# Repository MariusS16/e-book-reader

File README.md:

# README - OpenBook E-Reader

**Autor: Slincu Marius**

## Prezentare Generală

OpenBook este un e-reader open-source bazat pe microcontrollerul ESP32-C6. Dispozitivul integrează un ecran e-paper de 7.5 inch, un senzor de mediu (BME680), un sistem de monitorizare a bateriei, precum și conectivitate Wi-Fi și USB-C. Acest fisier descrie arhitectura hardware a proiectului, componentele principale și modul în care acestea sunt interconectate.

---

## Diagramă de Bloc

```

                +---------------------------+
                |     USB-C Connector       |
                | (USB Data ↔ ESP32 USB)    |
                | (ESD & Termination Prot.) |
                +-------------+-------------+
                              |
                              v
                +--------------------------+
                |       Charging IC        |<-- USB-C Power
                +-------------+------------+
                              |
                              v
                +--------------------------+
                |         Battery          |
                +-------------+------------+
                              |
                              v
                +--------------------------+
                |           LDO            |
                |       (3.3V Reg)         |
                +-------------+------------+
                              |
                              v
                      +--------------+
                      |    ESP32-C6   |
                      +------+--------+
                             |
      +----------------------+-------------------------+
      |                      |                         |
      v                      v                         v
+-----------+       +----------------+         +-----------------+
|  Display  |<----->|     BME688     |<------->| Tactile Buttons |
| (SPI 4W)  |       |   (I2C + PU)   |         |  (GPIO + RC)     |
+-----------+       +----------------+         +-----------------+
```

---
## Detalii Hardware

### ESP32-C6-WROOM-1-N8

- **Rol**: Componenta centrală de control, responsabilă pentru conectivitatea wireless și interacțiunea cu perifericele.
- **Interfețe disponibile**:
  - SPI: Utilizată pentru comunicarea cu ecranul e-paper, memoria Flash și cardul Micro SD.
  - I2C: Pentru conectarea senzorului BME680, monitorului de baterie (MAX17048) și ceasului RTC (DS3231).
  - GPIO: Utilizați pentru butoane de control și semnalizare prin LED-uri.
  - UART: Dedicat depanării și comunicației seriale.
- **Specificații tehnice**: Tactat la 160MHz, 512KB SRAM, 8MB memorie Flash integrată.

### Senzor BME680

- **Rol**: Oferă măsurători precise pentru temperatură, umiditate, presiune atmosferică și calitatea aerului.
- **Interfață**: Comunicare prin magistrala I2C cu viteză de 400kHz.
- **Eficiență energetică**: Consumă sub 1mA în funcționare și sub 1µA în repaus.

### Sistem de Alimentare

- **Baterie**: Acumulator Li-Po de 2500mAh, 3.7V.
- **Încărcare**: Controlată de MCP73831 prin portul USB-C, cu un curent maxim de 1A.
- **Monitorizare**: Realizată cu ajutorul cipului MAX17048, prin I2C.
- **Profil de consum**:
  - În activitate (Wi-Fi activ și ecran actualizat): ~150mA.
  - În standby (ecran static, fără activitate radio): ~10mA.
  - În modul deep sleep: >50µA.
  - **Autonomie estimată**: ~250 de ore la un consum mediu de 10mA.

### Butoane de Navigare

- Folosește butoane tactile Panasonic EVQPUJ02K, fiecare cu rezistență pull-up de 10KΩ.

### USB-C

- **Funcții**: Utilizat pentru încărcare (5V/1A) și transfer de date (USB 2.0).
- **Protecție**: Diode ESD (USBLC6-2SC6Y) pentru protejarea la supratensiuni.

---
# Lista de Componente (BOM)

Tabelul de mai jos prezintă componentele folosite în proiect:
| Component | Buy | Datasheet |
| ---------- | --------- | --------- |
| PFMF.050.1 | [Retailer](https://ro.mouser.com/ProductDetail/Schurter/PFMF.050.2?qs=1auRipcfynCums5v1iucSA%3D%3D) |  [Datasheet](https://ro.mouser.com/datasheet/2/358/typ_PFMF-1275918.pdf) |
| USB4110-GF-A | [Retailer](https://ro.mouser.com/ProductDetail/GCT/USB4110-GF-A?qs=KUoIvG%2F9IlYiZvIXQjyJeA%3D%3D) | [Datasheet](https://ro.mouser.com/datasheet/2/837/GCT_USB4110_Product_Drawing___20k_cycles-3455479.pdf) |
| USBLC6-2SC6Y | [Retailer](https://ro.mouser.com/ProductDetail/STMicroelectronics/USBLC6-2SC6Y?qs=gNDSiZmRJS%2FOgDexvXkdow%3D%3D) | [Datasheet](https://ro.mouser.com/datasheet/2/389/usblc6_2sc6y-1852505.pdf) |
| SD0805S020S1R0 | [Retailer](https://ro.mouser.com/ProductDetail/KYOCERA-AVX/SD0805S020S1R0?qs=jCA%252BPfw4LHbpkAoSnwrdjw%3D%3D) | [Datasheet](https://ro.mouser.com/datasheet/2/40/schottky-3165252.pdf) |
| DMG2305UX-7 | [Retailer](https://ro.mouser.com/ProductDetail/Diodes-Incorporated/DMG2305UX-7?qs=L1DZKBg7t5F%2FNBHrjfxC%252Bg%3D%3D) | [Datasheet](https://www.diodes.com/assets/Datasheets/DMG2305UX.pdf) |
| XC6220A331MR-G | [Retailer](https://ro.mouser.com/ProductDetail/Torex-Semiconductor/XC6220A331MR-G?qs=AsjdqWjXhJ8ZSWznL1J0gg%3D%3D) | [Datasheet](https://ro.mouser.com/datasheet/2/760/xc6220-3371556.pdf) |
| Condensator 100 uF TANT | [Retailer](https://ro.mouser.com/ProductDetail/KYOCERA-AVX/TAJW107M010RNJ?qs=Wtp%252Bf%2FAeVqIH8v1VxV%252B1Rg%3D%3D) | [Datasheet](https://ro.mouser.com/datasheet/2/40/TAJ-3165264.pdf) |
| 112A-TAAR-R03_ATTEND | [Retailer](https://www.digikey.ro/en/products/detail/attend-technology/112A-TAAR-R03/17633923) | [Datasheet](https://www.attend.com.tw/data/download/file/112A-TAAR-R03_Spec.pdf)
| ESP32-C6-WROOM-1-N8 | [Retailer](https://ro.mouser.com/ProductDetail/Espressif-Systems/ESP32-C6-WROOM-1-N8?qs=8Wlm6%252BaMh8ST02Gmwp74cw%3D%3D) | [Datasheet](https://ro.mouser.com/datasheet/2/891/Espressif_ESP32_C6_WROOM_1__Datasheet_V0_1_PRELIMI-3239987.pdf) |
| MCP73831 | [Retailer](https://ro.mouser.com/ProductDetail/Microchip-Technology/MCP73831T-2ACI-OT?qs=yUQqVecv4qvbBQBGbHx0Mw%3D%3D) | [Datasheet](https://ro.mouser.com/datasheet/2/268/MCP73831_Family_Data_Sheet_DS20001984H-3441711.pdf) |
| CHG_LED | [Retailer](https://store.comet.srl.ro/Catalogue/Product/40478/) | [Datasheet](https://www.snapeda.com/parts/KP-1608SURCK/Kingbright/datasheet/) |
| SI1308EDL-T1-GE3 | [Retailer](https://ro.mouser.com/ProductDetail/Vishay-Semiconductors/SI1308EDL-T1-GE3?qs=bX1%252BNvsK%2FBramh9tgpOaEw%3D%3D) | [Datasheet](https://www.vishay.com/doc?63399) |
| MBR0530 | [Retailer](https://ro.mouser.com/ProductDetail/Micro-Commercial-Components-MCC/MBR0530-T?qs=9VyI4qLX4NTSXkb9ynzJnA%3D%3D) | [Datasheet](https://ro.mouser.com/datasheet/2/258/mcc_mbr0520~mbr0560sod123-1179695.pdf) |
| L1 | [Retailer](https://ro.mouser.com/ProductDetail/Wurth-Elektronik/744043680?qs=PGXP4M47uW6VkZq%252BkzjrHA%3D%3D) | [Datasheet](https://www.we-online.com/components/products/datasheet/744043680.pdf) |
| FH34SRJ-24S-0.5SH_99_ | [Retailer](https://ro.mouser.com/ProductDetail/Hirose-Connector/FH34SRJ-24S-0.5SH99?qs=vcbW%252B4%252BSTIpKBl5ap9J8Fw%3D%3D) | [Datasheet](https://ro.mouser.com/datasheet/2/185/FH34SRJ_24S_0_5SH_99__CL0580_1255_6_99_2DDrawing_0-1615044.pdf) |
| BME688 | [Retailer](https://ro.mouser.com/ProductDetail/Bosch-Sensortec/BME688?qs=IS%252B4QmGtzzqQoVDscqwx3A%3D%3D) | [Datasheet](https://ro.mouser.com/datasheet/2/783/bst_bme688_fl000-2307034.pdf) |
| BD5229G-TR | [Retailer](https://ro.mouser.com/ProductDetail/ROHM-Semiconductor/BD5229G-TR?qs=4kLU8WoGk0vvnhrrYwdszw%3D%3D) | [Datasheet](https://fscdn.rohm.com/en/products/databook/datasheet/ic/power/voltage_detector/bd52xxg-e.pdf) |
| Button | [Retailer](https://ro.mouser.com/ProductDetail/CK/KMR221GULCLFS?qs=u2NJ%252B70r0goBXaNk7IrU0Q%3D%3D) | [Datasheet](https://www.ckswitches.com/media/1479/kmr2.pdf) |
| MAX17048G+T10 | [Retailer](https://ro.mouser.com/ProductDetail/Analog-Devices-Maxim-Integrated/MAX17048G%2bT10?qs=D7PJwyCwLAoGnnn8jEPRBQ%3D%3D) | [Datasheet](https://ro.mouser.com/datasheet/2/609/MAX17048_MAX17049-3469099.pdf) |
| W25Q512JVEIQ | [Retailer](https://ro.mouser.com/ProductDetail/Winbond/W25Q512JVEIQ?qs=l7cgNqFNU1jw6svr3at6tA%3D%3D) | [Datasheet](https://ro.mouser.com/datasheet/2/949/Winbond_W25Q512JV_Datasheet-3240039.pdf) |
| PGB1010603MR | [Retailer](https://ro.mouser.com/ProductDetail/Littelfuse/PGB1010603MRHF?qs=KvZd0dN2Zg%2FuIq6icj%252BGKA%3D%3D) | [Datasheet](https://www.littelfuse.com/media?resourcetype=datasheets&itemid=8a337998-d54d-466b-be4e-dc5bcd1f9321&filename=littelfuse_pulseguard_pgb1_datasheet.pdf) |
| QWIIC_RIGHT_ANGLE | [Retailer](https://ro.mouser.com/ProductDetail/GCT/USB4110-GF-A?qs=KUoIvG%2F9IlYiZvIXQjyJeA%3D%3D) | [Datasheet](https://ro.mouser.com/datasheet/2/837/GCT_USB4110_Product_Drawing___20k_cycles-3455479.pdf) |
| DS3231SN# | [Retailer](https://ro.mouser.com/ProductDetail/Analog-Devices-Maxim-Integrated/DS3231SN?qs=ffX8NcjNb2RmKAb9wAk9Ug%3D%3D) | [Datasheet](https://ro.mouser.com/datasheet/2/609/DS3231-3421123.pdf) |
| CPH3225A C10_SUPERCAP | [Retailer](https://ro.mouser.com/ProductDetail/Seiko-Semiconductors/CPH3225A?qs=3etwrb1wR%252BhUOph6lAO7eg%3D%3D) | [Datasheet](https://ro.mouser.com/datasheet/2/360/Seiko_Instruments_MicroBattery_E_20230330_2024Jan_-3561061.pdf) |
| Condensator 100nF | [Retailer](https://ro.mouser.com/ProductDetail/KYOCERA-AVX/06033G104ZAT2A?qs=NXubJDmysXJMPmHfVo6Z%252BA%3D%3D) | [Datasheet](https://ro.mouser.com/datasheet/2/40/KGM_Y5V-3223189.pdf) |
| Condensator 4.7uF | [Retailer](https://ro.mouser.com/ProductDetail/KYOCERA-AVX/0402ZD475MAT2A?qs=NBFAU1oqP4W4U2PCPHI0sg%3D%3D) | [Datasheet](https://ro.mouser.com/datasheet/2/40/cx5r_KGM-3223198.pdf) |
| Condensator 10uF | [Retailer](https://ro.mouser.com/ProductDetail/Samsung-Electro-Mechanics/CL10A106KQ8NNNL?qs=xZ%2FP%252Ba9zWqaes9JKSsob2Q%3D%3D) | [Datasheet](https://ro.mouser.com/datasheet/2/585/MLCC-1837944.pdf) |

## Configurare Pini ESP32-C6

| **Pin ESP32-C6** | **Funcție**         | **Componentă**         | **Rol**                                    |
|------------------|--------------------|------------------------|--------------------------------------------|
| GPIO0           | BOOT_BUTTON        | Buton                  | Activează modul de boot la inițializare    |
| GPIO1           | RESET_BUTTON       | Buton                  | Resetare manuală                           |
| GPIO2           | CHANGE_BUTTON      | Buton                  | Comutare între meniuri                     |
| GPIO3           | EPD_CS             | Display E-Paper        | Chip Select pentru SPI                     |
| GPIO4           | EPD_DC             | Display E-Paper        | Linie de control Date/Comenzi              |
| GPIO5           | EPD_RST            | Display E-Paper        | Reset hardware pentru ecran                |
| GPIO6           | EPD_BUSY           | Display E-Paper        | Semnal de stare pentru actualizare ecran   |
| GPIO7           | SPI_MOSI           | Display, Flash, SD     | Linie de date pentru SPI                   |
| GPIO8           | SPI_MISO           | Display, Flash, SD     | Linie de date SPI (citire)                 |
| GPIO9           | SPI_SCK            | Display, Flash, SD     | Semnal de ceas SPI                         |
| GPIO10          | FLASH_CS           | Memorie Flash          | Chip Select pentru memorie                 |
| GPIO11          | SD_CS              | Card Micro SD          | Chip Select pentru card SD                 |
| GPIO12          | I2C_SDA            | BME680, MAX17048, DS3231 | Linie de date I2C                         |
| GPIO13          | I2C_SCL            | BME680, MAX17048, DS3231 | Linie de ceas I2C                         |
| GPIO14          | CHG_LED            | LED                    | Indicator al procesului de încărcare       |
| GPIO15          | UART_TX            | Debugging              | Transmitere date prin UART                 |
| GPIO16          | UART_RX            | Debugging              | Recepție date prin UART                    |
| GPIO17          | USB_D+             | USB-C                  | Linie de date USB pozitivă                 |
| GPIO18          | USB_D-             | USB-C                  | Linie de date USB negativă                 |

**Notă**: Pinii sunt alocați conform specificațiilor ESP32-C6 și necesităților proiectului OpenBook. Mulți dintre ei pot îndeplini funcții multiple și pot fi configurați flexibil în funcție de aplicație.

**Notă**: Am avut o problema cu Fusion si mi-a dat crash aplicatia si am capatat o eroare de care nu am stiut sa scap si nu am mai putu contiuna modelul 3D, insa am facut partial din ea.

---

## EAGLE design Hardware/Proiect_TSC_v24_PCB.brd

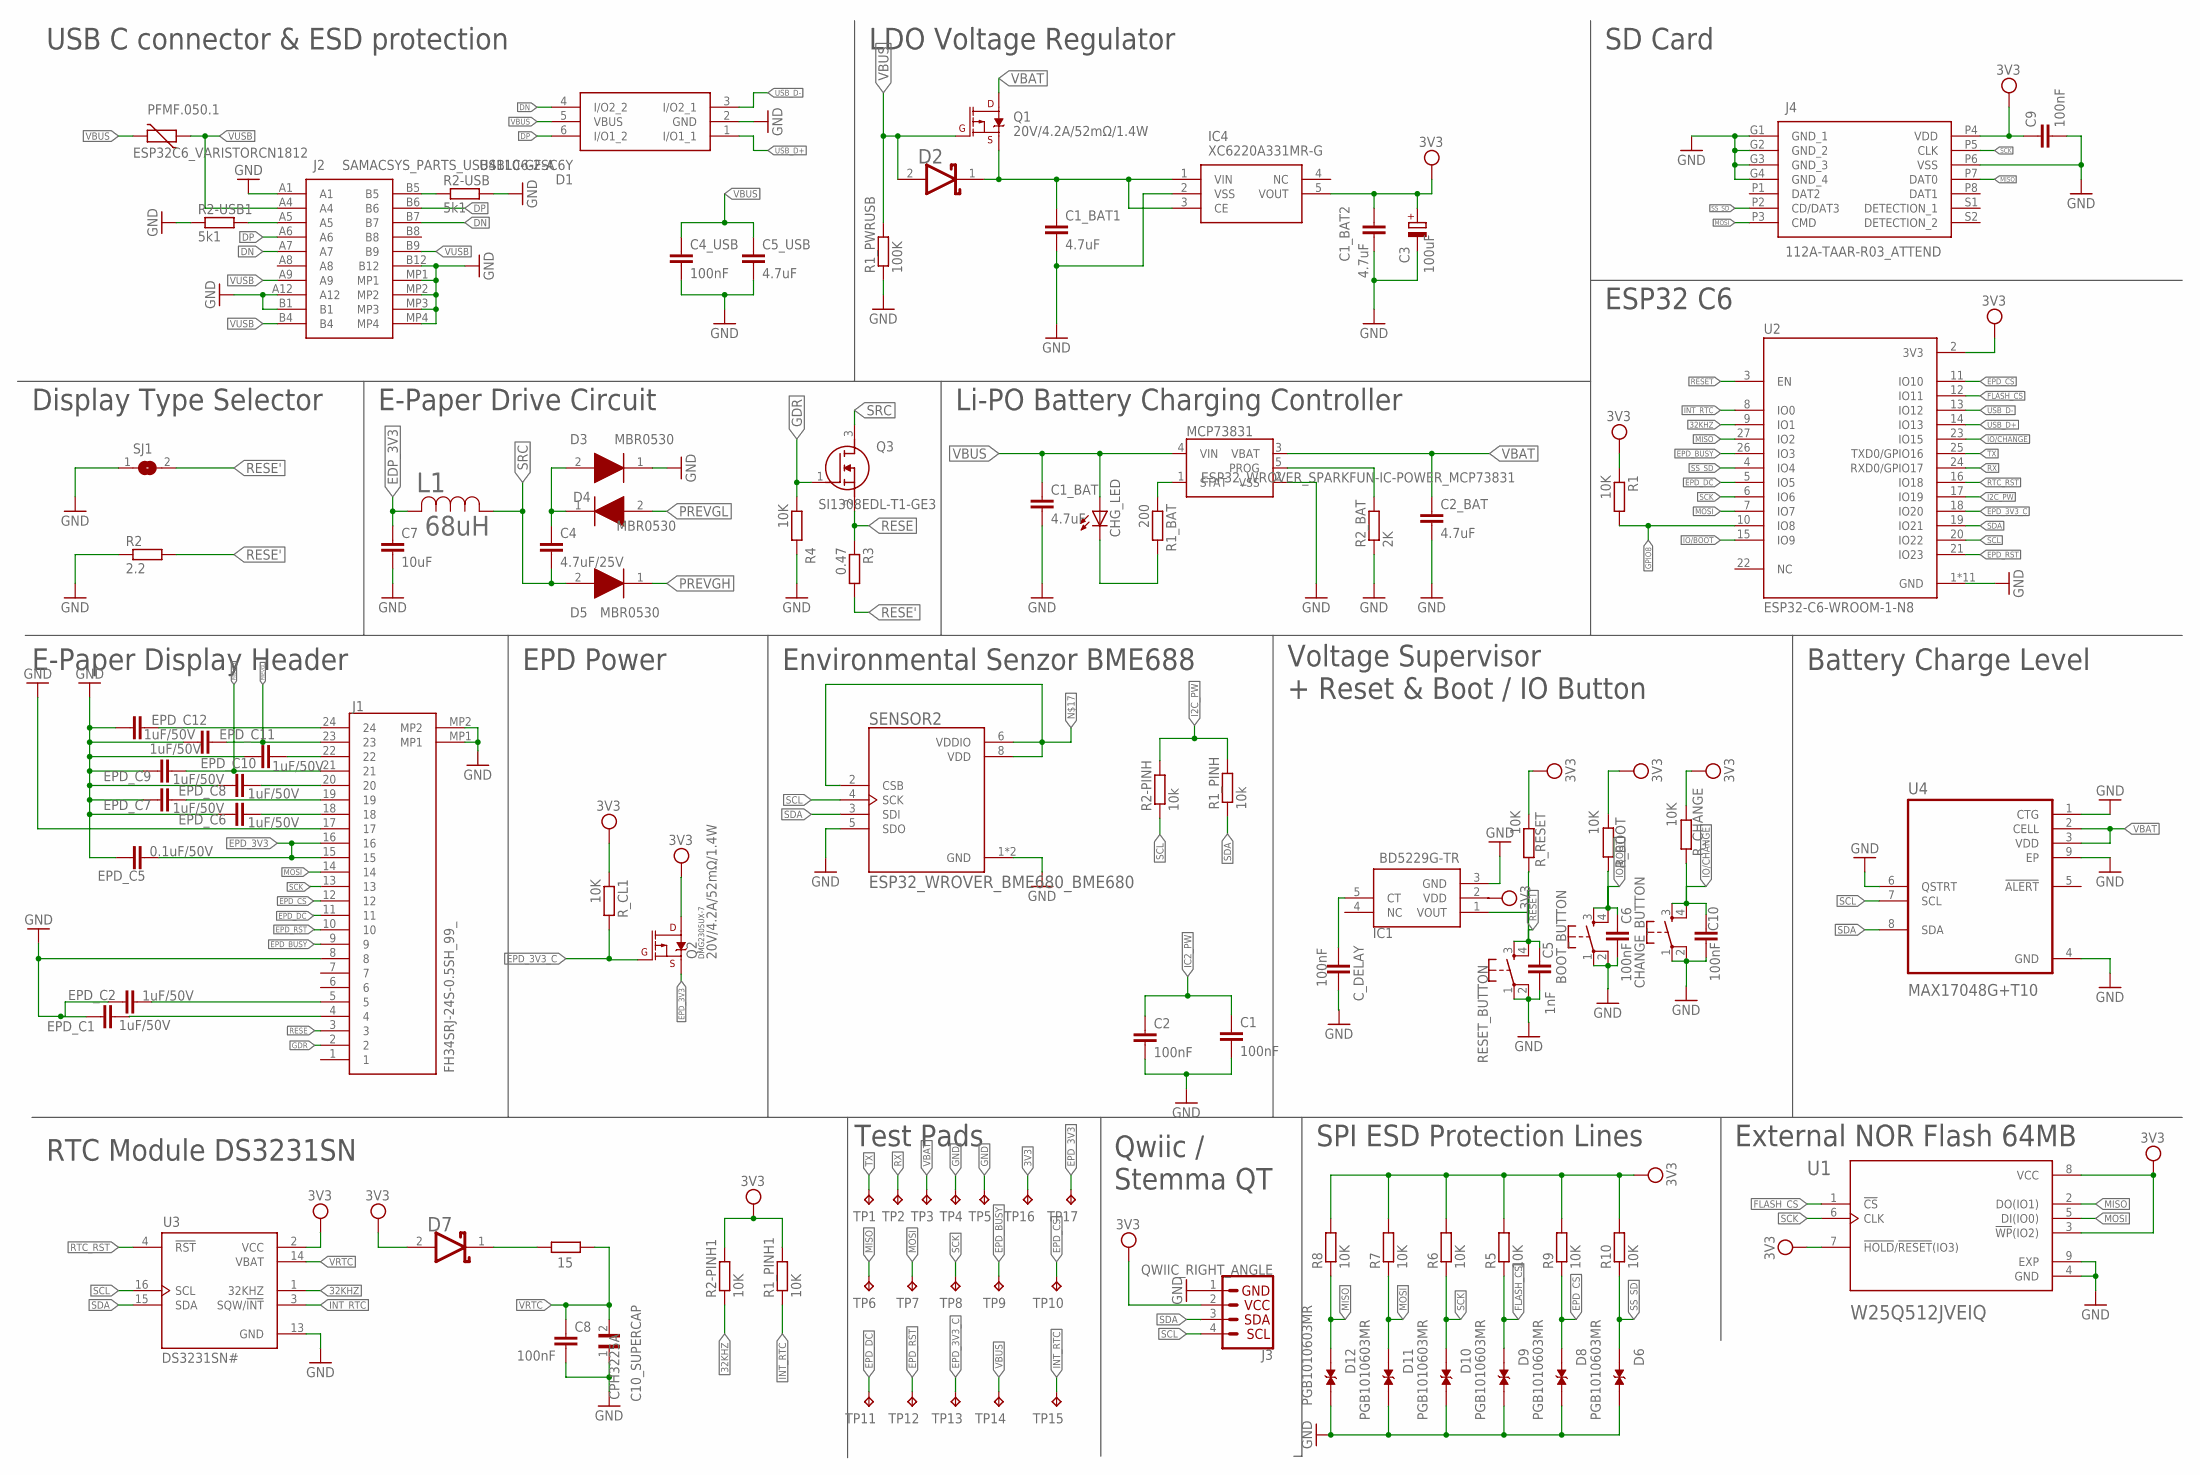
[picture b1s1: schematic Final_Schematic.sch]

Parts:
BOOT_BUTTON: BUTTON_CUSYOMV1; MYBUTTON
C1, C2, C4_USB, C8, C9: 100nF; ESP32_WROVER_EAGLE-LTSPICE_C0402
C1_BAT, C1_BAT1, C1_BAT2, C2_BAT, C5_USB: 4.7uF; ESP32_WROVER_EAGLE-LTSPICE_C0402
C3: 100uF; RCL_CT3528
C4: 4.7uF/25V; ESP32_WROVER_EAGLE-LTSPICE_C0402
C5: 1nF; EAGLE-LTSPICE_C0402
C6, C10: 100nF; EAGLE-LTSPICE_C0402
C7: 10uF; ESP32_WROVER_EAGLE-LTSPICE_C0402
C10_SUPERCAP: CPH3225A; CAPCP3225X100N
CHANGE_BUTTON: BUTTON_CUSYOMV1; MYBUTTON
CHG_LED: ADAFRUIT_LEDCHIP-LED0603; ADAFRUIT_CHIP-LED0603
C_DELAY: 100nF; ESP32_WROVER_EAGLE-LTSPICE_C0402
D1: USBLC6-2SC6Y; SOT95P280X145-6N
D2, D7: ESP32_WROVER_AVX---SD0805S020S1R0_AVX_SD0805S020S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; ESP32_WROVER_AVX---SD0805S020S1R0_AVX_SD0805S020S1R0_0
D3, D4, D5: MBR0530; SOD3716X135N
D6, D8, D9, D10, D11, D12: PGB1010603MR; DIOC1608X36N
EPD_C1, EPD_C2, EPD_C6, EPD_C7, EPD_C8, EPD_C9, EPD_C10, EPD_C11, EPD_C12: 1uF/50V; EAGLE-LTSPICE_C0402
EPD_C5: 0.1uF/50V; EAGLE-LTSPICE_C0402
IC1: BD5229G-TR; SOT95P280X125-5N
IC4: XC6220A331MR-G; SOT95P280X120-5N
J1: FH34SRJ-24S-0.5SH_99_; FH34SRJ24S05SH99
J2: SAMACSYS_PARTS_USB4110-GF-A; SAMACSYS_PARTS_USB4110GFA
J3: QWIIC_RIGHT_ANGLE; JST04_1MM_RA
J4: 112A-TAAR-R03_ATTEND; 112ATAARR03ATTEND
L1: 68uH; IND_4828-WE-TPC_WRE
MCP73831: ESP32_WROVER_SPARKFUN-IC-POWER_MCP73831; ESP32_WROVER_SPARKFUN-IC-POWER_SOT23-5
PFMF.050.1: ESP32C6_VARISTORCN1812; ESP32C6_VARISTOR_CT/CN1812
Q1, Q2: 20V/4.2A/52mΩ/1.4W; ESP32_WROVER_SPARKFUN-DISCRETESEMI_SOT23-3
Q3: SI1308EDL-T1-GE3; SOT65P210X110-3N
R1, R1_PINH1, R2-PINH1, R4, R5, R6, R7, R8, R9, R10: 10K; ESP32_WROVER_EAGLE-LTSPICE_R0402
R1_BAT: 200; ESP32_WROVER_EAGLE-LTSPICE_R0402
R1_PINH, R2-PINH: 10k; ESP32_WROVER_EAGLE-LTSPICE_R0402
R1_PWRUSB: 100K; ESP32_WROVER_EAGLE-LTSPICE_R0402
R2: 2.2; ESP32_WROVER_EAGLE-LTSPICE_R0402
R2-USB, R2-USB1: 5k1; ESP32_WROVER_EAGLE-LTSPICE_R0402
R2_BAT: 2K; ESP32_WROVER_EAGLE-LTSPICE_R0402
R3: 0.47; ESP32_WROVER_EAGLE-LTSPICE_R0402
RESET_BUTTON: BUTTON_CUSYOMV1; MYBUTTON
R_BOOT: 10K; ESP32_WROVER_EAGLE-LTSPICE_R0402
R_CAPACITOR: 15; ESP32_WROVER_EAGLE-LTSPICE_R0402
R_CHANGE: 10K; ESP32_WROVER_EAGLE-LTSPICE_R0402
R_CL1: 10K; ESP32_WROVER_EAGLE-LTSPICE_R0402
R_RESET: 10K; ESP32_WROVER_EAGLE-LTSPICE_R0402
SENSOR2: ESP32_WROVER_BME680_BME680; ESP32_WROVER_BME680_PSON80P300X300X100-8N
SJ1: SJ
TP1, TP2, TP3, TP4, TP5, TP6, TP7, TP8, TP9, TP10, TP11, TP12, TP13, TP14, TP15, TP16, TP17: TPTP20R; TP20R
U1: W25Q512JVEIQ; SON127P600X800X80-9N
U2: ESP32-C6-WROOM-1-N8; XCVR_ESP32-C6-WROOM-1-N8
U3: DS3231SN#; SOIC127P1032X265-16N
U4: MAX17048G+T10; SON50P200X200X80-9N

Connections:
3V3: C1_BAT2.1, C3.+, C9.1, D7.2 (ANODE), IC4.5 (VOUT), J3.2, J4.P4 (VDD), Q2.3 (D), R1.1, R1_PINH1.2, R2-PINH1.2, R5.2, R6.2, R7.2, R8.2, R9.2, R10.2, R_BOOT.2, R_CHANGE.2, R_CL1.1, R_RESET.2, TP16.TP, U1.3 (!WP!(IO2)), U1.7 (!HOLD!/!RESET!(IO3)), U1.8 (VCC), U2.2 (3V3), U3.2 (VCC)
32KHZ: R2-PINH1.1, U2.9 (IO1), U3.1 (32KHZ)
DN: D1.4 (I/O2_2), J2.A7, J2.B7
DP: D1.6 (I/O1_2), J2.A6, J2.B6
EDP_3V3: C7.1, L1.2
EPD_3V3: EPD_C5.2, J1.15, J1.16, Q2.2 (S), TP17.TP
EPD_3V3_C: Q2.1 (G), R_CL1.2, TP13.TP, U2.18 (IO20)
EPD_BUSY: J1.9, TP9.TP, U2.26 (IO3)
EPD_CS: D8.1, J1.12, R9.1, TP10.TP, U2.11 (IO10)
EPD_DC: J1.11, TP11.TP, U2.5 (IO5)
EPD_RST: J1.10, TP12.TP, U2.21 (IO23)
FLASH_CS: D9.1, R5.1, U1.1 (!CS), U2.12 (IO11)
GDR: J1.2, Q3.1 (G), R4.1
GND: BOOT_BUTTON.1, BOOT_BUTTON.2, C1.2, C1_BAT.2, C1_BAT1.2, C1_BAT2.2, C2.2, C2_BAT.2, C3.-, C4_USB.2, C5.2, C5_USB.2, C6.2, C7.2, C8.2, C9.2, C10.2, C10_SUPERCAP.1, CHANGE_BUTTON.1, CHANGE_BUTTON.2, C_DELAY.2, D1.2 (GND), D3.1 (K), D6.2, D8.2, D9.2, D10.2, D11.2, D12.2, EPD_C1.1, EPD_C2.1, EPD_C5.1, EPD_C6.1, EPD_C7.1, EPD_C8.1, EPD_C9.1, EPD_C10.1, EPD_C11.1, EPD_C12.1, IC1.3 (GND), IC4.2 (VSS), J1.8, J1.17, J1.MP1, J1.MP2, J2.A1, J2.A12, J2.B1, J2.B12, J2.MP1, J2.MP2, J2.MP3, J2.MP4, J3.1, J4.G1 (GND_1), J4.G2 (GND_2), J4.G3 (GND_3), J4.G4 (GND_4), J4.P6 (VSS), MCP73831.2 (VSS), R1_PWRUSB.1, R2.1, R2-USB.2, R2-USB1.1, R2_BAT.1, R4.2, RESET_BUTTON.1, RESET_BUTTON.2, SENSOR2.1 (GND), SENSOR2.5 (SDO), SENSOR2.7 (GND), SJ1.1, TP4.TP, TP5.TP, U1.4 (GND), U1.9 (EXP), U2.1 (GND), U2.28 (GND), U2.29_1 (GND), U2.29_2 (GND), U2.29_3 (GND), U2.29_4 (GND), U2.29_5 (GND), U2.29_6 (GND), U2.29_7 (GND), U2.29_8 (GND), U2.29_9 (GND), U3.13 (GND), U4.1 (CTG), U4.4 (GND), U4.6 (QSTRT), U4.9 (EP)
GPIO8: R1.2, U2.10 (IO8)
I2C_PW: R1_PINH.2, R2-PINH.2, U2.17 (IO19)
IC2_PW: C1.1, C2.1
INT_RTC: R1_PINH1.1, TP15.TP, U2.8 (IO0), U3.3 (SQW/!INT)
IO/BOOT: BOOT_BUTTON.3, BOOT_BUTTON.4, C6.1, R_BOOT.1, U2.15 (IO9)
IO/CHANGE: C10.1, CHANGE_BUTTON.3, CHANGE_BUTTON.4, R_CHANGE.1, U2.23 (IO15)
MISO: D12.1, J4.P7 (DAT0), R8.1, TP6.TP, U1.2 (DO(IO1)), U2.27 (IO2)
MOSI: D11.1, J1.14, J4.P3 (CMD), R7.1, TP7.TP, U1.5 (DI(IO0)), U2.7 (IO7)
unnamed: EPD_C10.2, J1.22
unnamed: C1_BAT1.1, D2.1 (CATHODE), IC4.1 (VIN), IC4.3 (CE), Q1.2 (S)
unnamed: MCP73831.5 (PROG), R2_BAT.2
unnamed: EPD_C8.2, J1.20
unnamed: J2.B5, R2-USB.1
unnamed: C4.1, D3.2 (A), D4.1 (K)
unnamed: MCP73831.1 (STAT), R1_BAT.1
unnamed: CHG_LED.C, R1_BAT.2
unnamed: EPD_C7.2, J1.19
unnamed: J2.A5, R2-USB1.2
unnamed: EPD_C6.2, J1.18
unnamed: EPD_C12.2, J1.24
unnamed: D7.1 (CATHODE), R_CAPACITOR.2
unnamed: EPD_C2.2, J1.5
unnamed: EPD_C1.2, J1.4
unnamed: SENSOR2.2 (CSB), SENSOR2.6 (VDDIO), SENSOR2.8 (VDD)
unnamed: C_DELAY.1, IC1.5 (CT)
PREVGH: D5.1 (K), EPD_C9.2, J1.21
PREVGL: D4.2 (A), EPD_C11.2, J1.23
RESE: J1.3, Q3.2 (S), R3.1
RESE': R2.2, R3.2, SJ1.2
RESET: C5.1, IC1.1 (VOUT), RESET_BUTTON.3, RESET_BUTTON.4, R_RESET.1, U2.3 (EN)
RTC_RST: U2.16 (IO18), U3.4 (!RST)
RX: TP2.TP, U2.24 (RXD0/GPIO17)
SCK: D10.1, J1.13, J4.P5 (CLK), R6.1, TP8.TP, U1.6 (CLK), U2.6 (IO6)
SCL: J3.4, R2-PINH.1, SENSOR2.4 (SCK), U2.20 (IO22), U3.16 (SCL), U4.7 (SCL)
SDA: J3.3, R1_PINH.1, SENSOR2.3 (SDI), U2.19 (IO21), U3.15 (SDA), U4.8 (SDA)
SRC: C4.2, D5.2 (A), L1.1, Q3.3 (D)
SS_SD: D6.1, J4.P2 (CD/DAT3), R10.1, U2.4 (IO4)
TX: TP1.TP, U2.25 (TXD0/GPIO16)
USB_D+: D1.1 (I/O1_1), U2.14 (IO13)
USB_D-: D1.3 (I/O2_1), U2.13 (IO12)
VBAT: C2_BAT.1, MCP73831.3 (VBAT), Q1.3 (D), TP3.TP, U4.2 (CELL), U4.3 (VDD)
VBUS: C1_BAT.1, C4_USB.1, C5_USB.1, CHG_LED.A, D1.5 (VBUS), D2.2 (ANODE), MCP73831.4 (VIN), PFMF.050.1.2, Q1.1 (G), R1_PWRUSB.2, TP14.TP
VRTC: C8.1, C10_SUPERCAP.2, R_CAPACITOR.1, U3.14 (VBAT)
VUSB: J2.A4, J2.A9, J2.B4, J2.B9, PFMF.050.1.1

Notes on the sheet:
USB C connector & ESD protection
LDO Voltage Regulator
SD Card
ESP32 C6
Li-PO Battery Charging Controller
Display Type Selector
E-Paper Drive Circuit
Battery Charge Level
External NOR Flash 64MB
E-Paper Display Header
DMG2305UX-7
EPD Power
Environmental Senzor BME688
Voltage Supervisor + Reset & Boot / IO Button
RTC Module DS3231SN
Qwiic / Stemma QT
Test Pads
SPI ESD Protection Lines

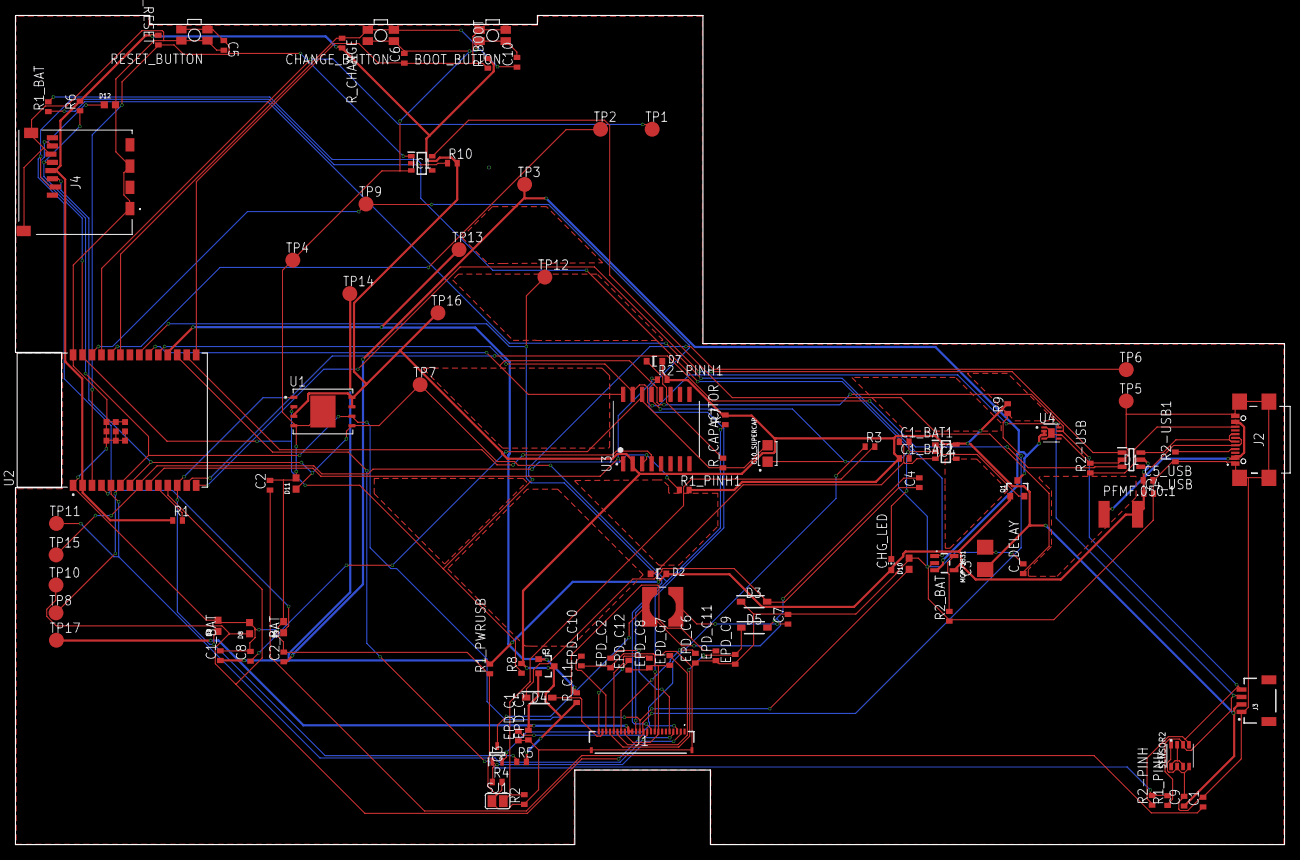
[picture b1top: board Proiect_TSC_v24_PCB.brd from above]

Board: 2 copper layers, 170.2 x 111.2 mm, 103 parts (0 on the bottom side), 58 nets.

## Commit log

2025-04-06 README2
2025-04-06 final
2025-04-06 Create LICENSE
2025-04-06 poze
2025-04-06 v2.2
2025-04-15 readmev2
2025-04-15 finalv2

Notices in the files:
parts and their libraries:
DeskAssistant v19 v1: COPYRIGHT: Copyright (C) 2024 Ultra Librarian. All rights reserved.
